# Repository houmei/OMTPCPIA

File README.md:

# OMTPCPIA and other TRRS plug converter (KiCad5)

Schematic

PCB

部品表  

J1 [基板用RCAジャック 黄 RJ-2410](https://akizukidenshi.com/catalog/g/gC-06508/)  
J2 [基板用RCAジャック 白 MJ-523](https://akizukidenshi.com/catalog/g/gC-16497/)  
J3 [基板用RCAジャック 赤 RJ-2410](https://akizukidenshi.com/catalog/g/gC-02385/)  
J5-J8 [３．５ｍｍ４極ミニジャック　基板取付用　ＭＪ－４ＰＰ－９](https://akizukidenshi.com/catalog/g/gC-06070/)  

## 説明

[OMTPCTIA 4極3.5mmジャックの変換基板](http://blog.livedoor.jp/hardyboy/archives/10368279.html)  

## 履歴
V01L01(非公開) 初版 RCAジャック、4極3.5mmジャックのフットプリント要改善  
V01L02 フットプリントのみ差し替え  

## OMTPCTIAV01L02GB - Gerber
JLCPCBなどにそのまま出図可能です。

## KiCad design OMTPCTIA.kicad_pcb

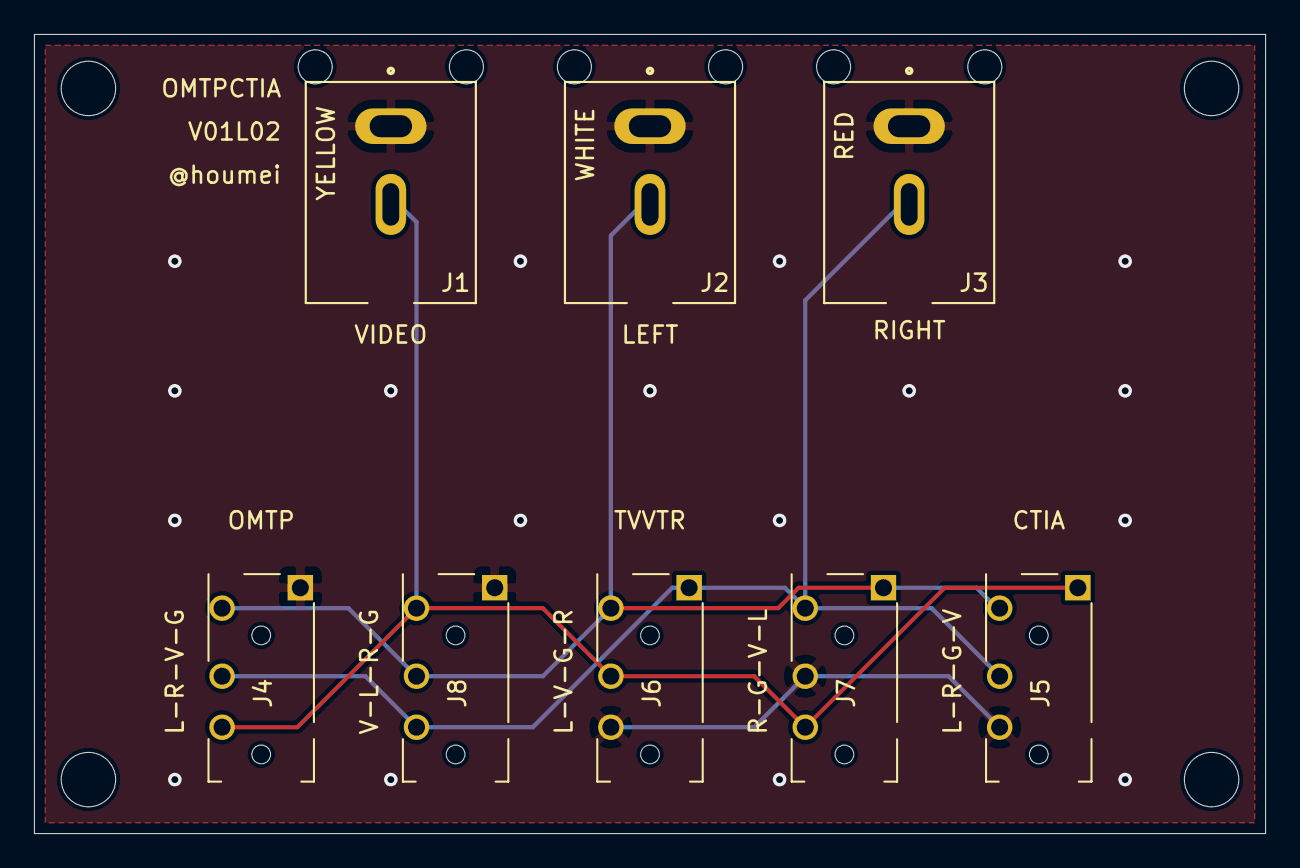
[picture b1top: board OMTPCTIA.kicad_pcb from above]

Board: 2 copper layers, 72.4 x 47.0 mm, 8 parts (0 on the bottom side), 4 nets.

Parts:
J1, J2, J3: Conn_Coaxial; MJ-523
J4, J5, J6, J7, J8: AudioJack4; Jack_3.5mm_MJ-4PP-9

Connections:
GND: J1.2, J2.2, J3.2, J4.S, J5.R2, J6.R2, J7.R1, J8.S
L: J2.1, J4.T, J5.T, J6.T, J7.S, J8.R1
R: J3.1, J4.R1, J5.R1, J6.S, J7.T, J8.R2
V: J1.1, J4.R2, J5.S, J6.R1, J7.R2, J8.T

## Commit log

2023-06-09 rename img
